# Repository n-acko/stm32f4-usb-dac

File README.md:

STM32F401 USB Audio Stereo DAC

STM32F401RCT6 based PCB with PCM1780 DAC and DRV602 line driver.
Hardware folder contains Kicad project and manufacturing files for PCB.
Software folder contains STM32CudeIDE project for firmware.
Board supports 16/24bit audio depth and 44.1/48/96KHz audio frequency.

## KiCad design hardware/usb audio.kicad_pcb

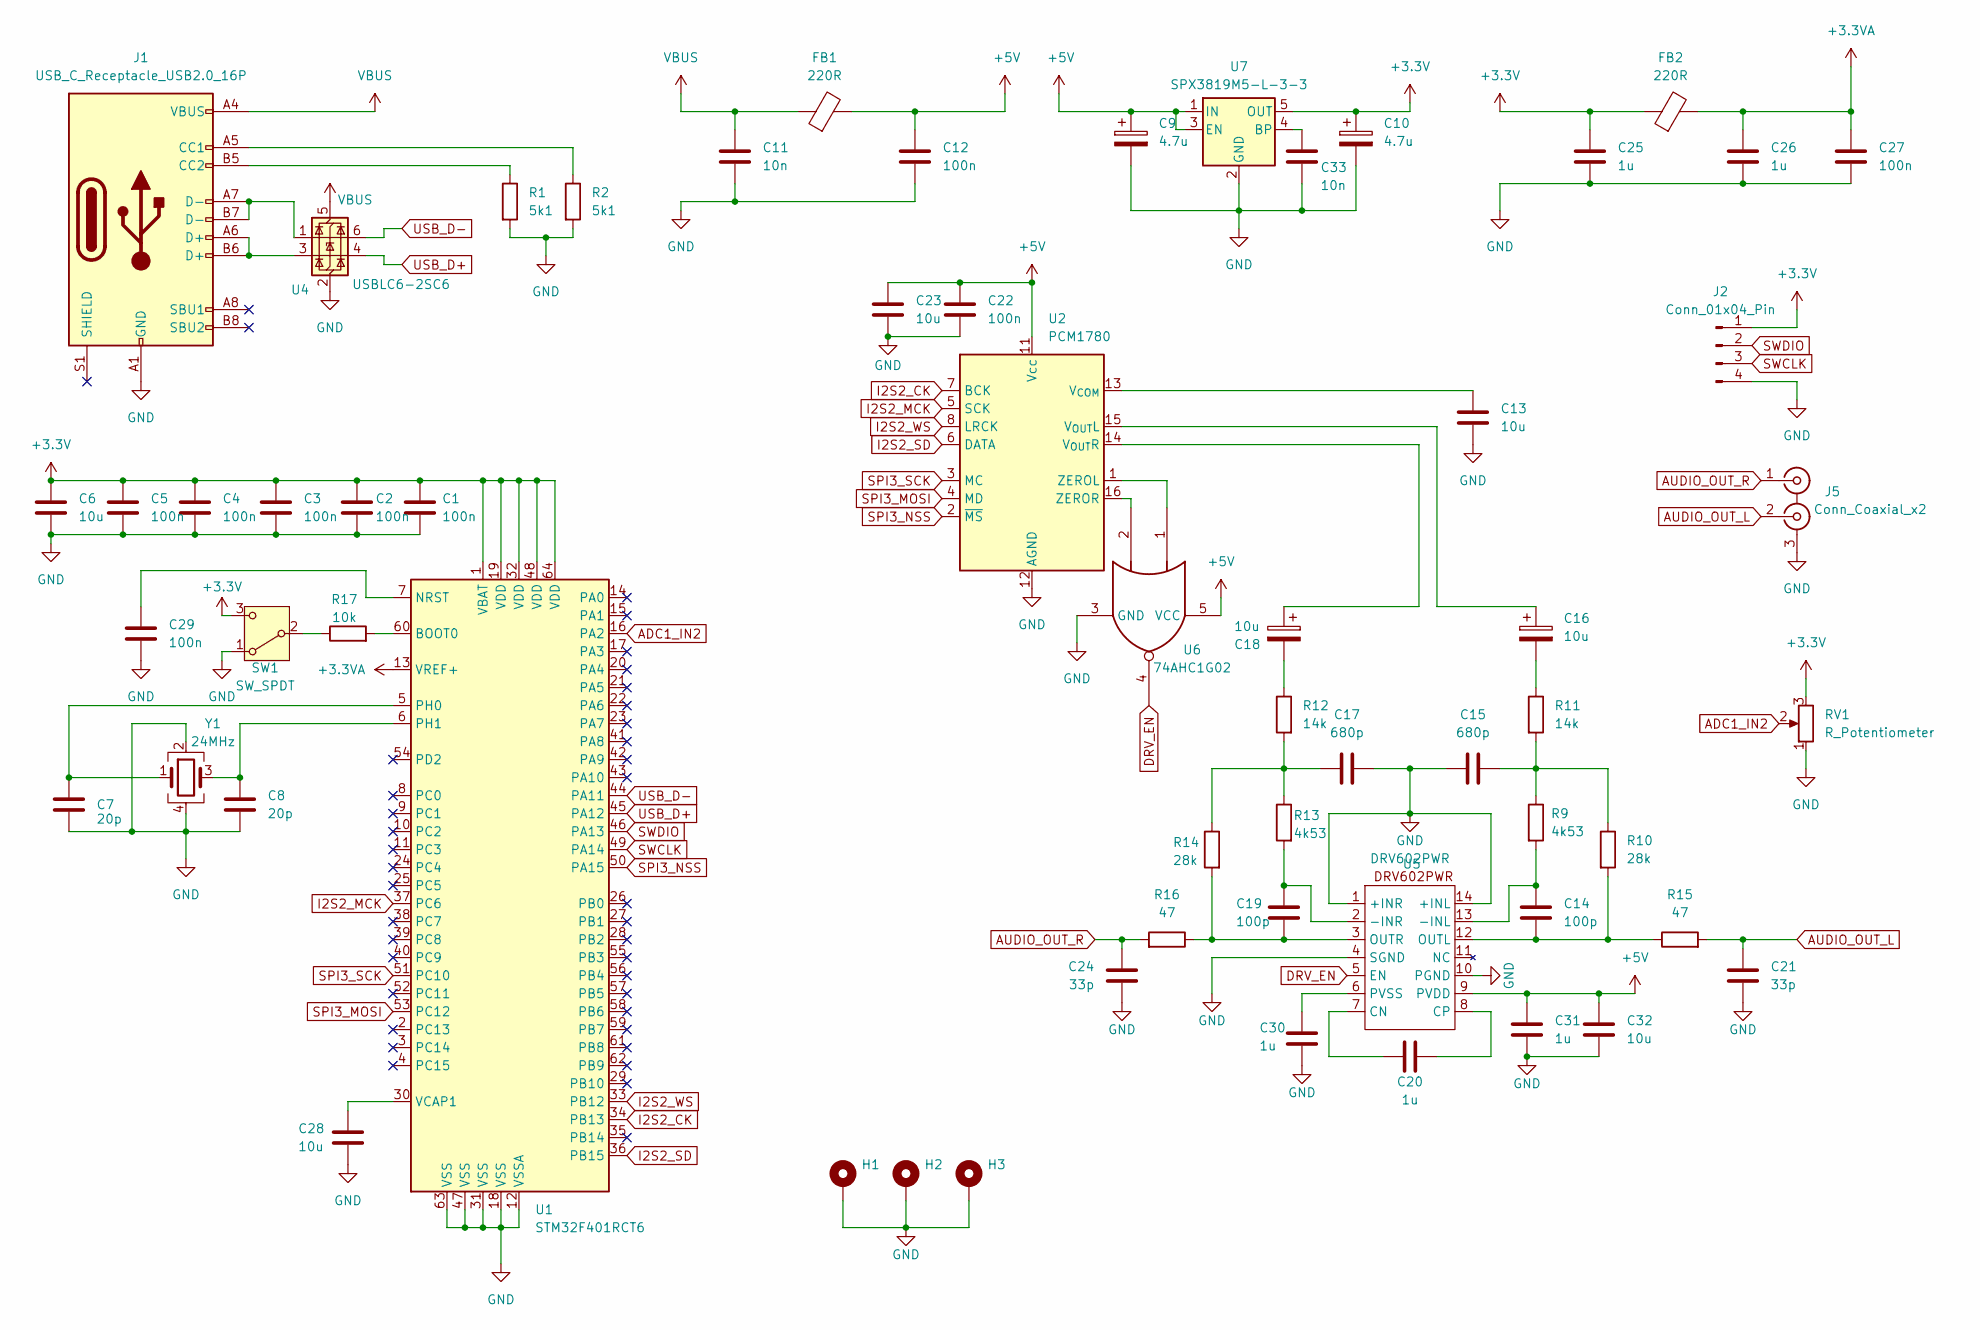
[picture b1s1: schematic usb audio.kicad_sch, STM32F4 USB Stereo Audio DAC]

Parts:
C1, C2, C3, C4, C5, C12, C22, C27, C29: 100n; C_0402_1005Metric
C6, C13, C23, C28, C32: 10u; C_0805_2012Metric
C7, C8: 20p; C_0402_1005Metric
C9, C10: 4.7u; CP_Elec_4x5.4
C11, C33: 10n; C_0402_1005Metric
C14, C19: 100p; C_0402_1005Metric
C15, C17: 680p; C_0402_1005Metric
C16, C18: 10u; CP_Elec_3x5.4
C20, C25, C26: 1u; C_0805_2012Metric
C21, C24: 33p; C_0402_1005Metric
C30, C31: 1u; C_0603_1608Metric
FB1, FB2: 220R; L_0603_1608Metric
H1, H2, H3: MountingHole_Pad; MountingHole_2.2mm_M2_Pad_Via
J1: USB_C_Receptacle_USB2.0_16P; USB_C_Receptacle_G-Switch_GT-USB-7010ASV
J2: Conn_01x04_Pin; PinHeader_1x04_P2.54mm_Vertical
J5: Conn_Coaxial_x2; XDJK-0271-1650
R1, R2: 5k1; R_0603_1608Metric
R9, R13: 4k53; R_0402_1005Metric
R10, R14: 28k; R_0402_1005Metric
R11, R12: 14k; R_0402_1005Metric
R15, R16: 47; R_0603_1608Metric
R17: 10k; R_0603_1608Metric
RV1: R_Potentiometer; Potentiometer_Alps_RK163_Single_Horizontal
SW1: SW_SPDT; JS102011JCQN
U1: STM32F401RCT6; LQFP-64_10x10mm_P0.5mm
U2: PCM1780; SSOP-16_3.9x4.9mm_P0.635mm
U4: USBLC6-2SC6; SOT-23-6
U5: DRV602PWR; TSSOP-14_4.4x5mm_P0.65mm
U6: 74AHC1G02; SOT-23-5
U7: SPX3819M5-L-3-3; SOT-23-5
Y1: 24MHz; Crystal_SMD_3225-4Pin_3.2x2.5mm

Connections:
+3.3V: C1.1, C2.1, C3.1, C4.1, C5.1, C6.1, C10.1, C25.1, FB2.1, J2.1, RV1.3, SW1.3 (C), U1.1 (VBAT), U1.19 (VDD), U1.32 (VDD), U1.48 (VDD), U1.64 (VDD), U7.5 (OUT)
+3.3VA: C26.1, C27.1, FB2.2, U1.13 (VREF+)
+5V: C9.1, C12.1, C22.1, C23.1, C31.1, C32.1, FB1.2, U2.11 (Vcc), U5.9 (PVDD), U6.5 (VCC), U7.1 (IN), U7.3 (EN)
ADC1_IN2: RV1.2, U1.16 (PA2)
AUDIO_OUT_L: C21.1, J5.2 (IN2), R15.2
AUDIO_OUT_R: C24.1, J5.1 (IN1), R16.2
DRV_EN: U5.5 (EN), U6.4
GND: C1.2, C2.2, C3.2, C4.2, C5.2, C6.2, C7.2, C8.2, C9.2, C10.2, C11.2, C12.2, C13.2, C15.1, C17.1, C21.2, C22.2, C23.2, C24.2, C25.2, C26.2, C27.2, C28.2, C29.2, C30.2, C31.2, C32.2, C33.2, H1.1, H2.1, H3.1, J1.A1 (GND), J1.A12 (GND), J1.B1 (GND), J1.B12 (GND), J2.4, J5.3 (EXT), R1.2, R2.2, RV1.1, SW1.1 (A), U1.12 (VSSA), U1.18 (VSS), U1.31 (VSS), U1.47 (VSS), U1.63 (VSS), U2.12 (AGND), U4.2 (GND), U5.1 (+INR), U5.4 (SGND), U5.10 (PGND), U5.14 (+INL), U6.3 (GND), U7.2 (GND), Y1.2, Y1.4
I2S2_CK: U1.34 (PB13), U2.7 (BCK)
I2S2_MCK: U1.37 (PC6), U2.5 (SCK)
I2S2_SD: U1.36 (PB15), U2.6 (DATA)
I2S2_WS: U1.33 (PB12), U2.8 (LRCK)
unnamed: C15.2, R9.1, R10.1, R11.2
unnamed: C16.2, R11.1
unnamed: C17.2, R12.2, R13.1, R14.1
unnamed: C18.2, R12.1
unnamed: J1.A5 (CC1), R2.1
unnamed: J1.B5 (CC2), R1.1
unnamed: J1.A6 (D+), J1.B6 (D+), U4.3 (I/O2)
unnamed: J1.A7 (D-), J1.B7 (D-), U4.1 (I/O1)
unnamed: R17.1, SW1.2 (B)
unnamed: R17.2, U1.60 (BOOT0)
unnamed: C29.1, U1.7 (NRST)
unnamed: C7.1, U1.5 (PH0), Y1.1
unnamed: C8.1, U1.6 (PH1), Y1.3
unnamed: C28.1, U1.30 (VCAP1)
unnamed: C13.1, U2.13 (V_{COM})
unnamed: C16.1, U2.15 (V_{OUT}L)
unnamed: C18.1, U2.14 (V_{OUT}R)
unnamed: U2.1 (ZEROL), U6.1
unnamed: U2.16 (ZEROR), U6.2
unnamed: C14.1, R9.2, U5.13 (-INL)
unnamed: C19.1, R13.2, U5.2 (-INR)
unnamed: C20.2, U5.7 (CN)
unnamed: C20.1, U5.8 (CP)
unnamed: C14.2, R10.2, R15.1, U5.12 (OUTL)
unnamed: C19.2, R14.2, R16.1, U5.3 (OUTR)
unnamed: C30.1, U5.6 (PVSS)
unnamed: C33.1, U7.4 (BP)
SPI3_MOSI: U1.53 (PC12), U2.4 (MD)
SPI3_NSS: U1.50 (PA15), U2.2 (~MS)
SPI3_SCK: U1.51 (PC10), U2.3 (MC)
SWCLK: J2.3, U1.49 (PA14)
SWDIO: J2.2, U1.46 (PA13)
USB_D+: U1.45 (PA12), U4.4 (I/O2)
USB_D-: U1.44 (PA11), U4.6 (I/O1)
VBUS: C11.1, FB1.1, J1.A4 (VBUS), J1.A9 (VBUS), J1.B4 (VBUS), J1.B9 (VBUS), U4.5 (VBUS)

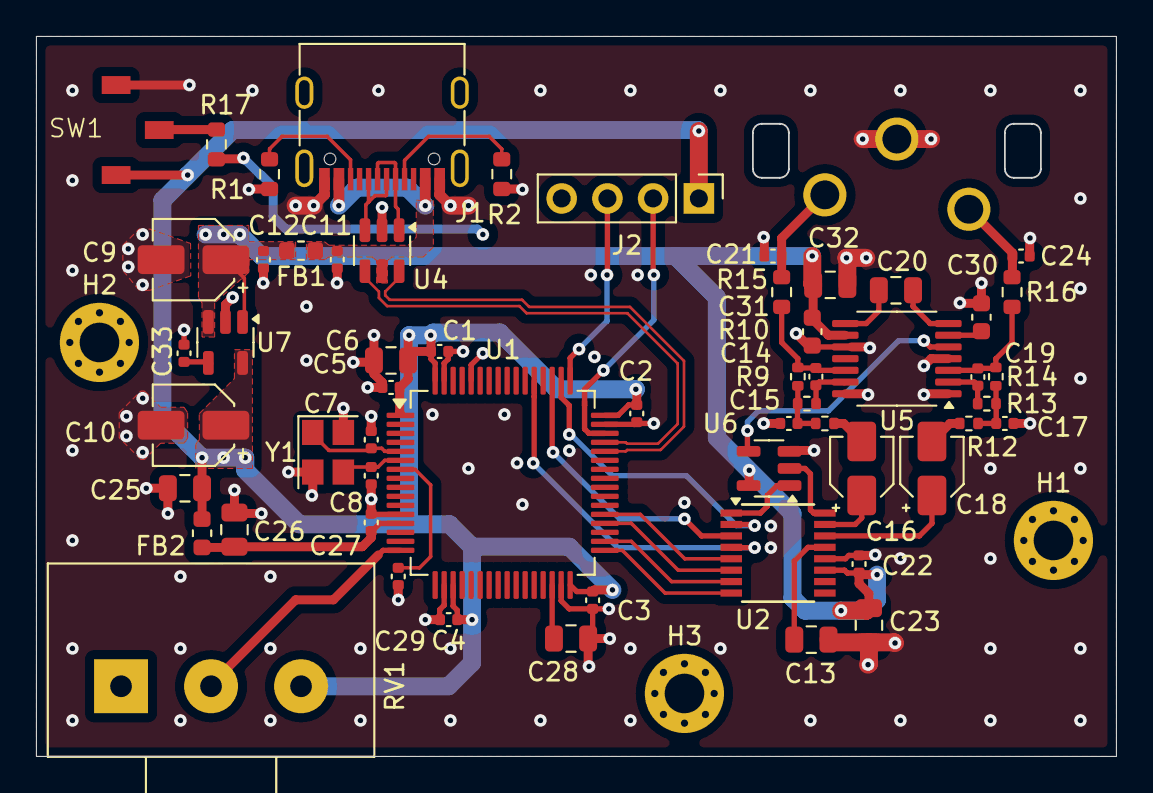
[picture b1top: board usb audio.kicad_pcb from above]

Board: 4 copper layers, 60.0 x 40.0 mm, 61 parts (0 on the bottom side), 47 nets.

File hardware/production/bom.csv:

Designator,Footprint,Quantity,Value,LCSC Part #
"C1, C12, C2, C22, C27, C29, C3, C4, C5",0402,9,100n,C77020
"C10, C9",CP_Elec_4x5.4,2,4.7u,C72511
"C11, C33",0402,2,10n,C1524
"C13, C23, C28, C32, C6",0805,5,10u,C15850
"C14, C19",0402,2,100p,C327198
"C15, C17",0402,2,680p,C782153
"C16, C18",CP_Elec_3x5.4,2,10u,C250999
"C20, C25, C26",0805,3,1u,C215803
"C21, C24",0402,2,33p,C107005
"C30, C31",0603,2,1u,C15849
"C7, C8",0402,2,20p,C182483
"FB1, FB2",0603,2,220R,C80165
J1,USB_C_Receptacle_G-Switch_GT-USB-7010ASV,1,USB_C_Receptacle_USB2.0_16P,C2988369
J2,PinHeader_1x04_P2.54mm_Vertical,1,Conn_01x04_Pin,C7501582
J5,XDJK-0271-1650,1,Conn_Coaxial_x2,C7527522
"R1, R2",0603,2,5k1,C844933
"R10, R14",0402,2,28k,C2998150
"R11, R12",0402,2,14k,C226789
"R13, R9",0402,2,4k53,C416543
"R15, R16",0603,2,47,C114623
R17,0603,1,10k,C844918
RV1,Potentiometer_Alps_RK163_Single_Horizontal,1,R_Potentiometer,C3007973
SW1,JS102011JCQN,1,SW_SPDT,C221659
U1,LQFP-64_10x10mm_P0.5mm,1,STM32F401RCT6,C74524
U2,SSOP-16_3.9x4.9mm_P0.635mm,1,PCM1780,C130014
U4,SOT-23-6,1,USBLC6-2SC6,C2827654
U5,TSSOP-14_4.4x5mm_P0.65mm,1,DRV602PWR,C129432
U6,SOT-23-5,1,74AHC1G02,C7463
U7,SOT-23-5,1,SPX3819M5-L-3-3,C9055
Y1,Crystal_SMD_3225-4Pin_3.2x2.5mm,1,24MHz,C7466181

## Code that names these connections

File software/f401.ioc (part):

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Mcu.Name=STM32F401R(B-C)Tx
Mcu.Package=LQFP64
Mcu.UserName=STM32F401RCTx
PA11.Mode=Device_Only
PA11.Signal=USB_OTG_FS_DM
PA12.Mode=Device_Only
PA12.Signal=USB_OTG_FS_DP
PA13.Mode=Serial_Wire
PA13.Signal=SYS_JTMS-SWDIO
PA14.Mode=Serial_Wire
PA14.Signal=SYS_JTCK-SWCLK
PA15.GPIOParameters=GPIO_Speed,PinState,GPIO_Label
PA15.GPIO_Label=NCS
PA15.GPIO_Speed=GPIO_SPEED_FREQ_MEDIUM
PA15.PinState=GPIO_PIN_SET
PA15.Signal=GPIO_Output
PA2.Signal=ADCx_IN2
PB12.GPIOParameters=GPIO_Speed
PB12.GPIO_Speed=GPIO_SPEED_FREQ_LOW
PB12.Mode=Half_Duplex_Master
PB12.Signal=I2S2_WS
PB13.GPIOParameters=GPIO_Speed
PB13.GPIO_Speed=GPIO_SPEED_FREQ_LOW
PB13.Mode=Half_Duplex_Master
PB13.Signal=I2S2_CK
PB15.GPIOParameters=GPIO_Speed
PB15.GPIO_Speed=GPIO_SPEED_FREQ_LOW
PB15.Mode=Half_Duplex_Master
PB15.Signal=I2S2_SD
PC10.GPIOParameters=GPIO_Speed,PinState,GPIO_Label
PC10.GPIO_Label=CLOCK
PC10.GPIO_Speed=GPIO_SPEED_FREQ_MEDIUM
PC10.PinState=GPIO_PIN_SET
PC10.Signal=GPIO_Output
PC12.GPIOParameters=GPIO_Speed,GPIO_Label
PC12.GPIO_Label=SDATA
PC12.GPIO_Speed=GPIO_SPEED_FREQ_MEDIUM
PC12.Signal=GPIO_Output
PC6.GPIOParameters=GPIO_Speed
PC6.GPIO_Speed=GPIO_SPEED_FREQ_LOW
PC6.Mode=Master_Clock_Activated
PC6.Signal=I2S2_MCK
PH0\ -\ OSC_IN.Mode=HSE-External-Oscillator
PH0\ -\ OSC_IN.Signal=RCC_OSC_IN
PH1\ -\ OSC_OUT.Mode=HSE-External-Oscillator
PH1\ -\ OSC_OUT.Signal=RCC_OSC_OUT
RCC.HSE_VALUE=24000000
RCC.SYSCLKFreq_VALUE=84000000
RCC.SYSCLKSource=RCC_SYSCLKSOURCE_PLLCLK
board=custom
